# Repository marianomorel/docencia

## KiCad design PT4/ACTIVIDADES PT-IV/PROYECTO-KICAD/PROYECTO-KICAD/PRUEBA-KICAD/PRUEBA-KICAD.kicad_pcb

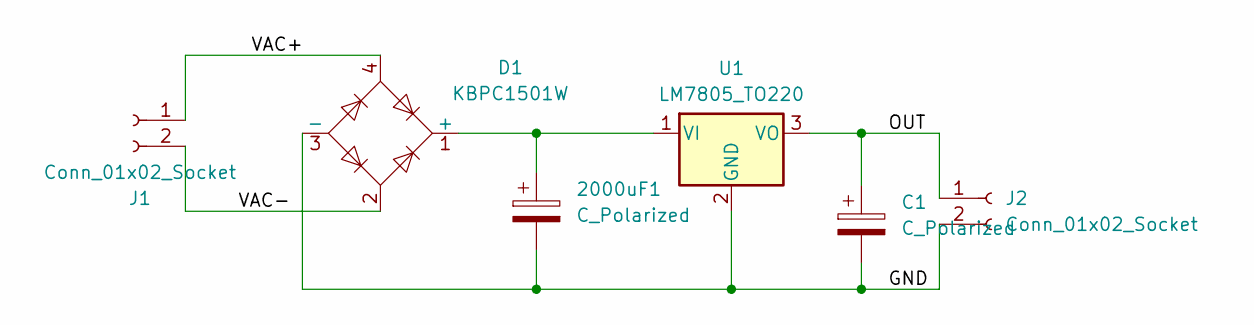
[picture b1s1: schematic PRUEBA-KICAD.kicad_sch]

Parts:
2000uF1: C_Polarized; C_Radial_D18.0mm_H35.5mm_P7.50mm
C1: C_Polarized; C_Radial_D5.0mm_H11.0mm_P2.00mm
D1: KBPC1501W; Diode_Bridge_GeneSiC_KBPC_W
J1, J2: Conn_01x02_Socket; TerminalBlock_MaiXu_MX126-5.0-02P_1x02_P5.00mm
U1: LM7805_TO220; TO-220-3_Vertical

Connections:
/GND: 2000uF1.2, C1.2, D1.3 (-), J2.2, U1.2 (GND)
/OUT: C1.1, J2.1, U1.3 (VO)
/VAC+: D1.4, J1.1
/VAC-: D1.2, J1.2
unnamed: 2000uF1.1, D1.1 (+), U1.1 (VI)

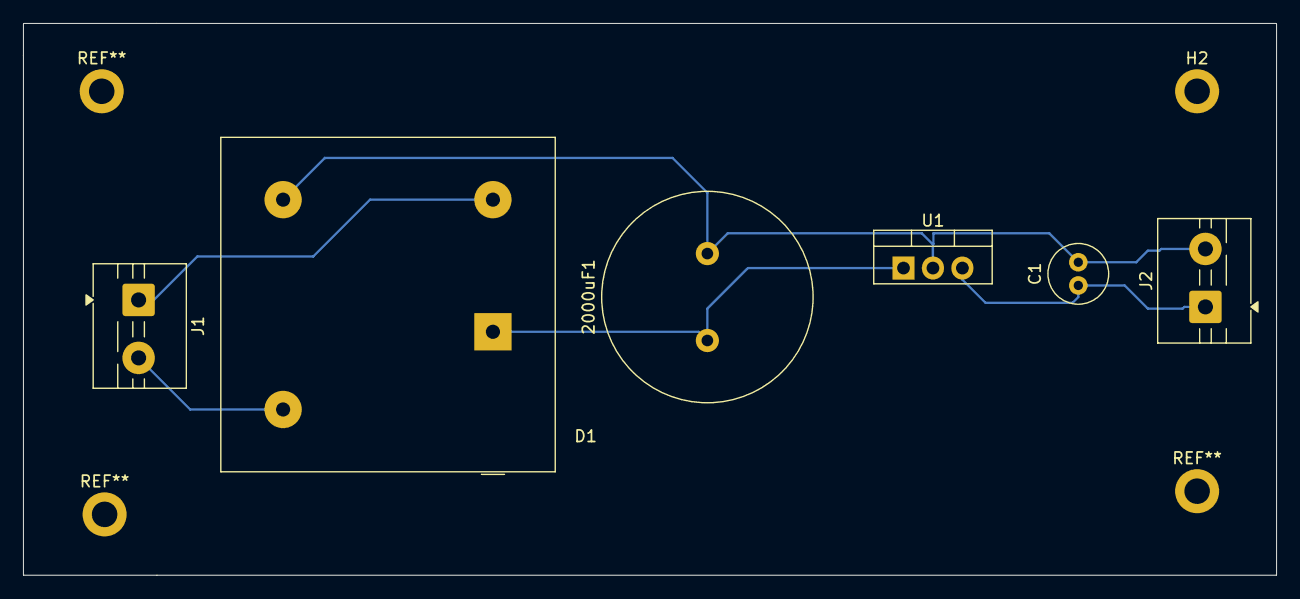
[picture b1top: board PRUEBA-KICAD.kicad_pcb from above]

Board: 2 copper layers, 108.1 x 47.6 mm, 7 parts (0 on the bottom side), 5 nets.

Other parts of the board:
H2: MountingHole_2.2mm_M2_DIN965_Pad

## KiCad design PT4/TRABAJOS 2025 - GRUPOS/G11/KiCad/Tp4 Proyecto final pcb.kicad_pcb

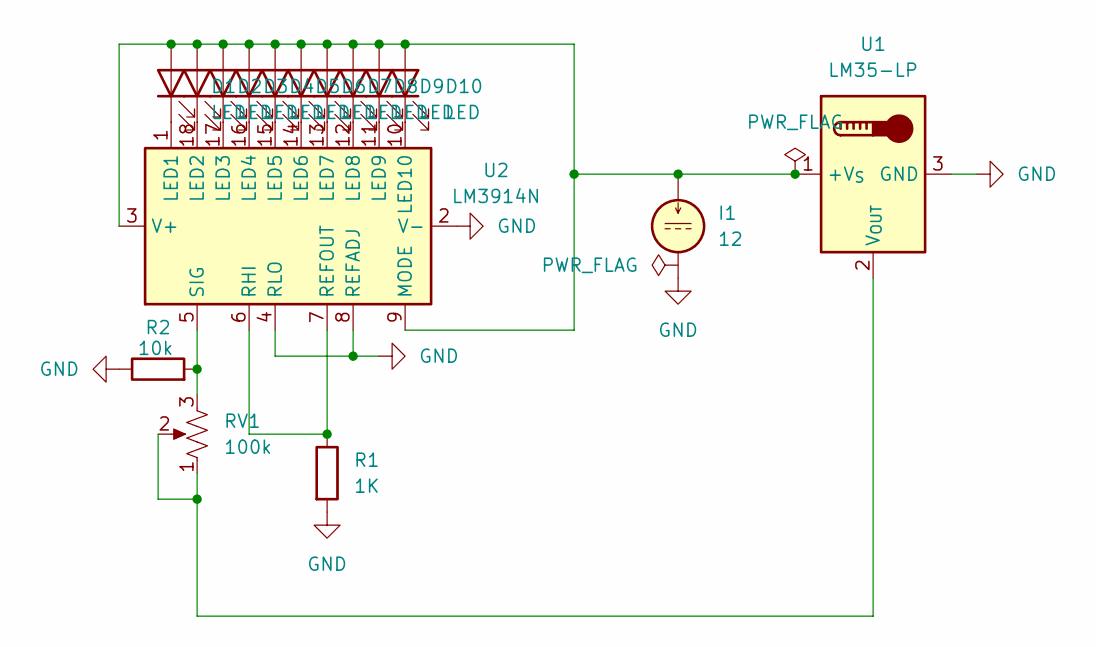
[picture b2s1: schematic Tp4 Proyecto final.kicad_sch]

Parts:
D1, D2, D3, D4, D5, D6, D7, D8, D9, D10: LED; LED_D5.0mm
I1: 12; SolderWire-0.1sqmm_1x02_P3.6mm_D0.4mm_OD1mm
R1: 1K; R_LDR_5.2x5.2mm_P3.5mm_Horizontal
R2: 10k; R_LDR_5.2x5.2mm_P3.5mm_Horizontal
RV1: 100k; Potentiometer_Piher_PT-10-V05_Vertical
U1: LM35-LP; TO-92_Inline_Wide
U2: LM3914N; DIP-18_W7.62mm

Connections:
GND: I1.2, R1.2, R2.1, U1.3 (GND), U2.2 (V-), U2.4 (RLO), U2.8 (REFADJ)
unnamed: D1.2 (A), D2.2 (A), D3.2 (A), D4.2 (A), D5.2 (A), D6.2 (A), D7.2 (A), D8.2 (A), D9.2 (A), D10.2 (A), I1.1, U1.1 (+V_{S}), U2.3 (V+), U2.9 (MODE)
unnamed: D1.1 (K), U2.1 (LED1)
unnamed: D2.1 (K), U2.18 (LED2)
unnamed: D3.1 (K), U2.17 (LED3)
unnamed: D4.1 (K), U2.16 (LED4)
unnamed: D5.1 (K), U2.15 (LED5)
unnamed: D6.1 (K), U2.14 (LED6)
unnamed: D7.1 (K), U2.13 (LED7)
unnamed: D8.1 (K), U2.12 (LED8)
unnamed: D9.1 (K), U2.11 (LED9)
unnamed: D10.1 (K), U2.10 (LED10)
unnamed: RV1.1, RV1.2, U1.2 (V_{OUT})
unnamed: R1.1, U2.6 (RHI), U2.7 (REFOUT)
unnamed: R2.2, RV1.3, U2.5 (SIG)

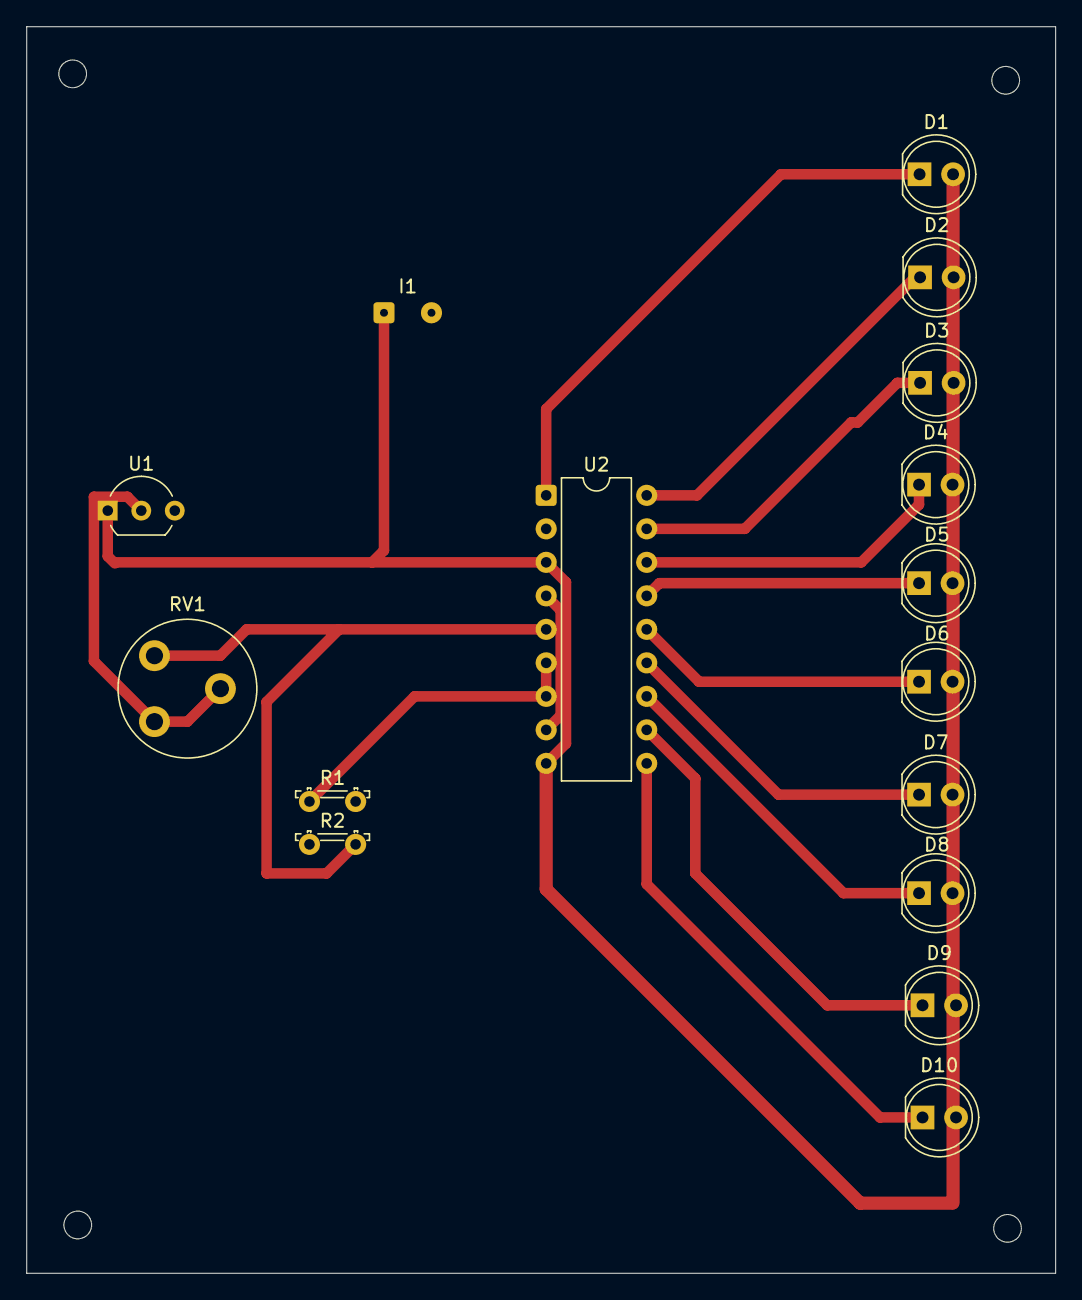
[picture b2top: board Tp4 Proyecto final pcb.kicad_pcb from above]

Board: 2 copper layers, 78.0 x 94.5 mm, 16 parts (0 on the bottom side), 15 nets.

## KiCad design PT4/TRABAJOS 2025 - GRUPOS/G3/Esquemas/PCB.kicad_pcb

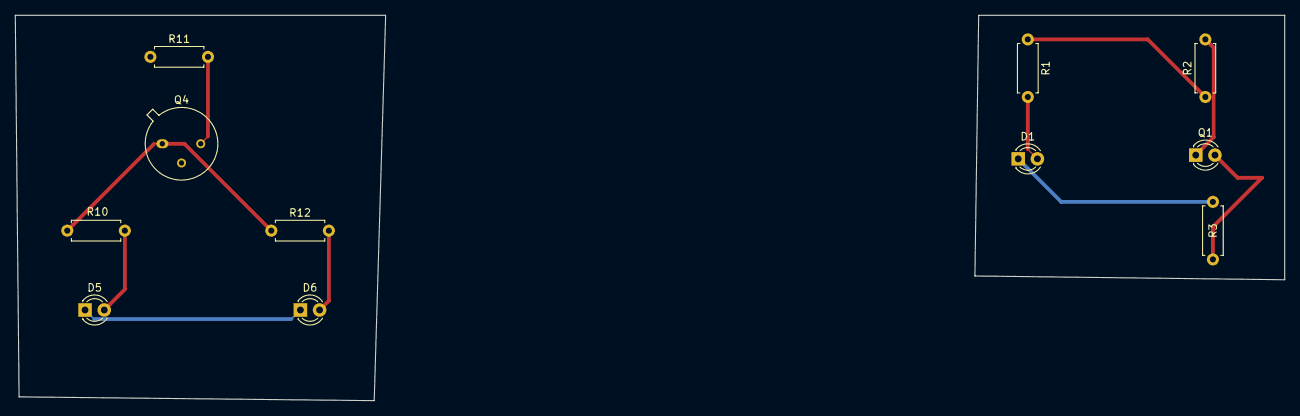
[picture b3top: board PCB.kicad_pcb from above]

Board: 2 copper layers, 168.0 x 51.0 mm, 11 parts (0 on the bottom side), 9 nets.

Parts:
D1, D5, D6: IR204A; LED_D3.0mm_IRBlack
Q1: TEPT4400; LED_D3.0mm_Clear
Q4: 2N2219; TO-39-3
R1, R2, R10, R12: 220; R_Axial_DIN0207_L6.3mm_D2.5mm_P7.62mm_Horizontal
R3, R11: 10k; R_Axial_DIN0207_L6.3mm_D2.5mm_P7.62mm_Horizontal

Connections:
+5V: R1.1, R2.1, R11.1
GND: D1.1 (K), D5.1 (K), D6.1 (K), R3.2
unnamed: Q1.2 (E), R3.1
unnamed: D1.2 (A), R1.2
unnamed: D5.2 (A), R10.2
unnamed: D6.2 (A), R12.2
unnamed: Q1.1 (C), R2.2
unnamed: Q4.3 (C), R11.2
unnamed: Q4.1 (E), R10.1, R12.1

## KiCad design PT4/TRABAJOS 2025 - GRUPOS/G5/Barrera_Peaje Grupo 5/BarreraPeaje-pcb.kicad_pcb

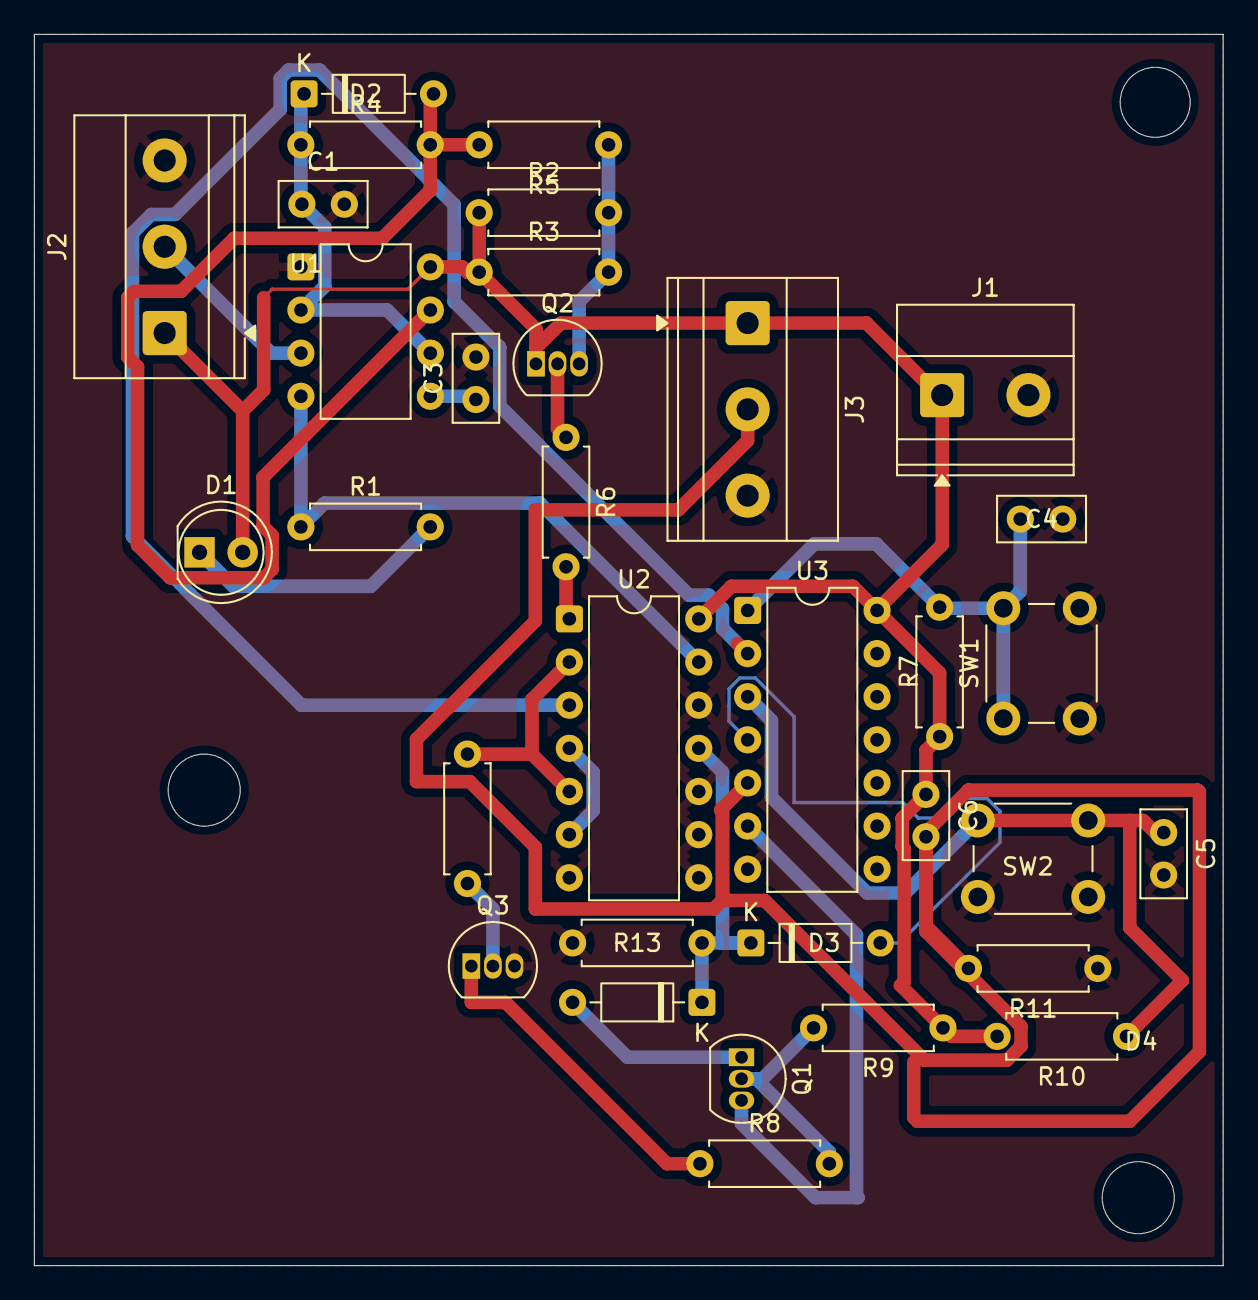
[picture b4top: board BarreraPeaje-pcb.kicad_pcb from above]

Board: 2 copper layers, 70.0 x 72.5 mm, 33 parts (0 on the bottom side), 24 nets.

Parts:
C1: 10nF; C_Disc_D5.0mm_W2.5mm_P2.50mm
C3, C4, C5, C6: 100nF; C_Disc_D5.0mm_W2.5mm_P2.50mm
D1: LED; LED_D5.0mm
D2, D3, D4: 1N4148; D_DO-35_SOD27_P7.62mm_Horizontal
J1: Alimentacion 12V; TerminalBlock_Phoenix_MKDS-1,5-2-5.08_1x02_P5.08mm_Horizont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
J2: Salida/Servo; TerminalBlock_Phoenix_MKDS-1,5-3-5.08_1x03_P5.08mm_Horizont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
J3: Sensor en Barrera; TerminalBlock_Phoenix_MKDS-1,5-3-5.08_1x03_P5.08mm_Horizont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
Q1: BC558; TO-92_Inline
Q2, Q3: BC548; TO-92_Inline
R1, R6, R7, R10, R11, R13: 10k; R_Axial_DIN0207_L6.3mm_D2.5mm_P7.62mm_Horizontal
R2: 47k; R_Axial_DIN0207_L6.3mm_D2.5mm_P7.62mm_Horizontal
R3, R9: 15k; R_Axial_DIN0207_L6.3mm_D2.5mm_P7.62mm_Horizontal
R4: 270k; R_Axial_DIN0207_L6.3mm_D2.5mm_P7.62mm_Horizontal
R5: 180; R_Axial_DIN0207_L6.3mm_D2.5mm_P7.62mm_Horizontal
R8, R12: 1k; R_Axial_DIN0207_L6.3mm_D2.5mm_P7.62mm_Horizontal
SW1: Open/Close; SW_PUSH_6mm_H4.3mm
SW2: Marcha/Stop; SW_PUSH_6mm_H4.3mm
U1: LM555xN; DIP-8_W7.62mm
U2: 4013; DIP-14_W7.62mm
U3: 40106; DIP-14_W7.62mm

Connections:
+5V: C6.1, D1.2 (A), J1.1, J2.1, J3.1, Q2.1 (C), R2.1, R3.1, R7.1, R9.1, R10.2, U1.8 (VCC), U2.14 (VDD), U3.14 (VDD)
GND: C1.2, C3.2, C4.2, C5.2, J1.2, J2.3, J3.3, Q3.3 (E), R11.1, R13.2, SW1.2, SW2.1, U1.1 (GND), U2.7 (VSS), U2.8 (S), U2.9 (D), U2.10 (R), U2.12 (~Q), U3.7 (VSS)
unnamed: C4.1, R7.2, SW1.1, U3.1
unnamed: C5.1, R10.1, SW2.2, U3.3
unnamed: D1.1 (K), R1.2
unnamed: D2.2 (A), R4.2, R5.2, U1.7 (DIS)
unnamed: C1.1, D2.1 (K), R4.1, U1.2 (TR), U1.6 (THR)
unnamed: D3.2 (A), U3.4
unnamed: D3.1 (K), D4.1 (K), R13.1, U2.11 (C)
unnamed: D4.2 (A), Q1.1 (C)
unnamed: J2.2, U1.3 (Q)
unnamed: C6.2, J3.2, R11.2, U3.5
unnamed: Q1.2 (B), R8.2, R9.2
unnamed: Q1.3 (E), U3.6
unnamed: Q2.2 (B), R6.1
unnamed: Q2.3 (E), R2.2, R3.2, R5.1
unnamed: Q3.2 (B), R12.2
unnamed: Q3.1 (C), R8.1
unnamed: C3.1, U1.5 (CV)
unnamed: R1.1, U1.4 (R), U2.13 (Q)
unnamed: U2.3 (C), U3.2
unnamed: R12.1, U2.2 (~Q), U2.5 (D)
unnamed: R6.2, U2.1 (Q)
unnamed: U2.4 (R), U2.6 (S)

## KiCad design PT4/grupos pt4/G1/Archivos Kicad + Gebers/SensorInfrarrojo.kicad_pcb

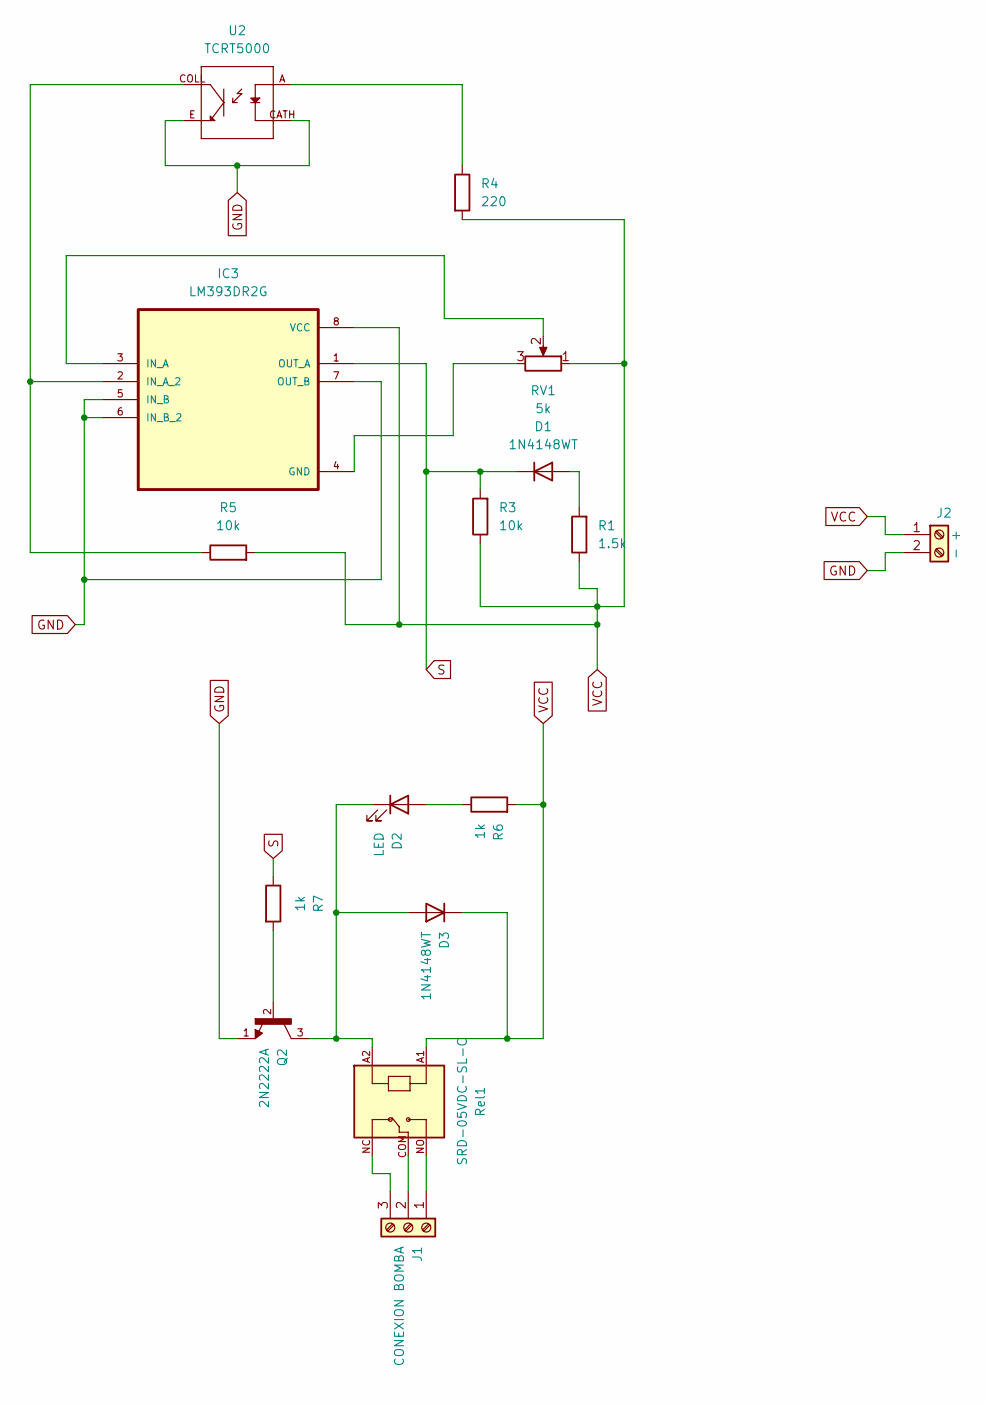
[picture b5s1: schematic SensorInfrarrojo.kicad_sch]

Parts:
D1, D3: 1N4148WT; D_SOD-523
D2: LED; LED_0402_1005Metric_Pad0.77x0.64mm_HandSolder
IC3: LM393DR2G; SOIC127P600X265-8N
J1: CONEXION BOMBA; TerminalBlock_Phoenix_MKDS-1,5-3_1x03_P5.00mm_Horizontal
J2: - +; TerminalBlock_MaiXu_MX126-5.0-02P_1x02_P5.00mm
Q2: 2N2222A; TO92254P470H750-3; PARTREV N/A
R1: 1.5k; R_0603_1608Metric_Pad0.98x0.95mm_HandSolder
R3, R5: 10k; R_0603_1608Metric_Pad0.98x0.95mm_HandSolder
R4: 220; R_0603_1608Metric_Pad0.98x0.95mm_HandSolder
R6, R7: 1k; R_Axial_DIN0204_L3.6mm_D1.6mm_P5.08mm_Horizontal
RV1: 5k; Potentiometer_Bourns_3296W_Vertical
Rel1: SRD-05VDC-SL-C; RELAY_SRD-05VDC-SL-C
U2: TCRT5000; OPTO_TCRT5000; PARTREV 1.7

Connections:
GND: IC3.5 (IN_B), IC3.6 (IN_B_2), IC3.7 (OUT_B), J2.2, Q2.1, U2.CATH, U2.E
unnamed: D1.2 (A), R1.2
unnamed: D2.2 (A), R6.1
unnamed: D2.1 (K), D3.2 (A), Q2.3, Rel1.A2
unnamed: IC3.4 (GND), RV1.3
unnamed: IC3.3 (IN_A), RV1.2
unnamed: IC3.2 (IN_A_2), R5.1, U2.COLL
unnamed: J1.1, Rel1.NO
unnamed: J1.2, Rel1.COM
unnamed: J1.3, Rel1.NC
unnamed: Q2.2, R7.2
unnamed: R4.1, U2.A
S: D1.1 (K), IC3.1 (OUT_A), R3.2, R7.1
VCC: D3.1 (K), IC3.8 (VCC), J2.1, R1.1, R3.1, R4.2, R5.2, R6.2, RV1.1, Rel1.A1

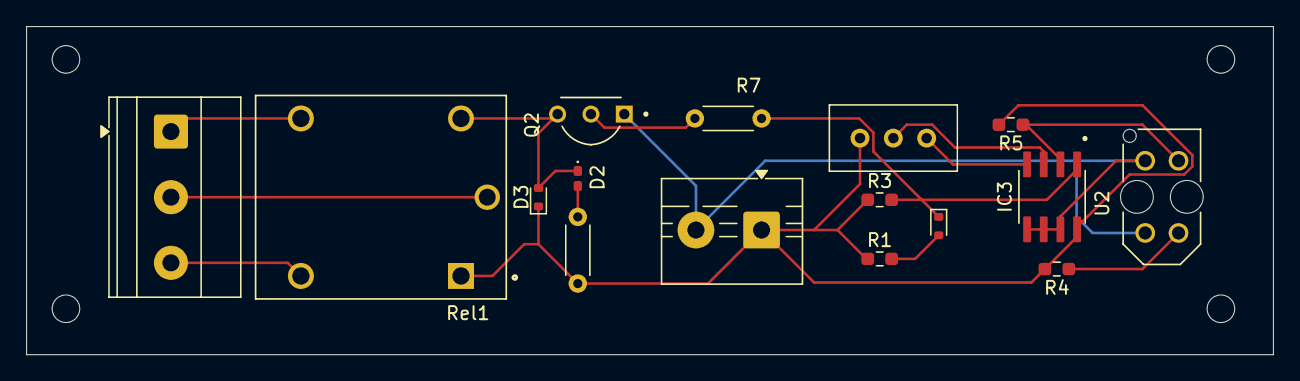
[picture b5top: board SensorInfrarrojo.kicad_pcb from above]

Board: 2 copper layers, 95.0 x 25.0 mm, 16 parts (0 on the bottom side), 14 nets.

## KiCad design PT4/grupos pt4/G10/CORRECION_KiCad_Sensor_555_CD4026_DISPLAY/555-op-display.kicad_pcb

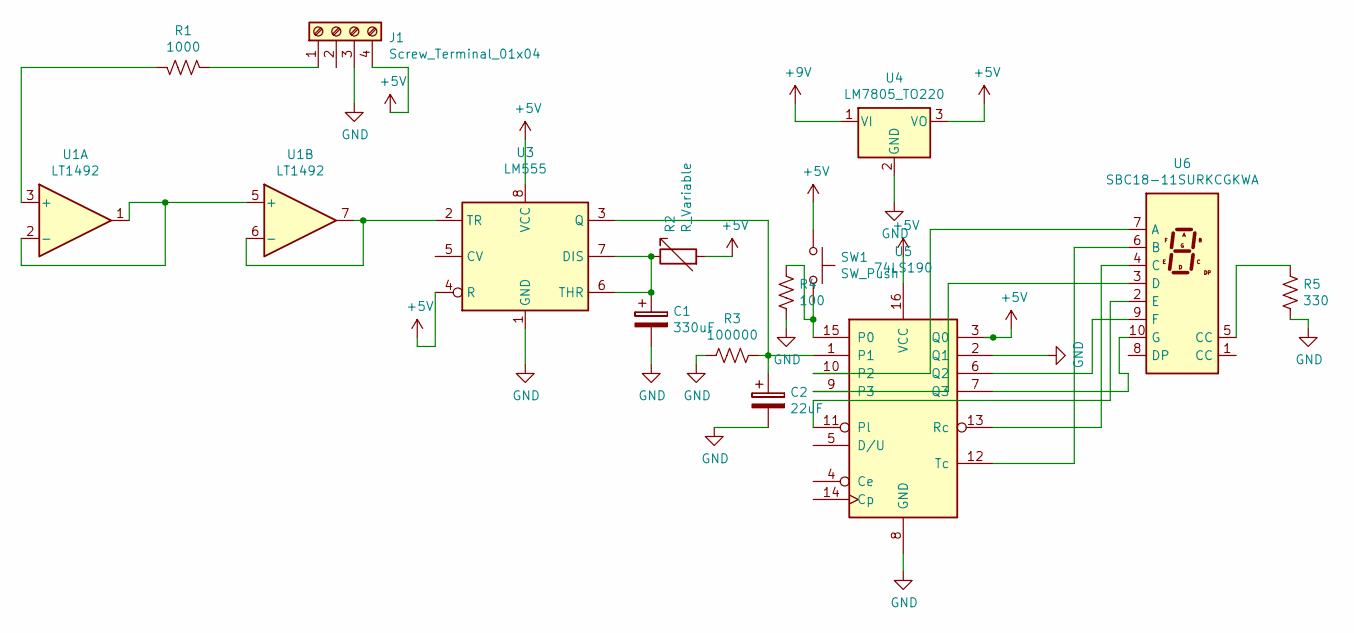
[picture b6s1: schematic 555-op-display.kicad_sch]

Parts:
C1: 330uF; CP_Radial_D5.0mm_P2.50mm
C2: 22uF; CP_Radial_D5.0mm_P2.50mm
J1: Screw_Terminal_01x04; TerminalBlock_bornier-4_P5.08mm
R1: 1000; R_Axial_DIN0204_L3.6mm_D1.6mm_P5.08mm_Horizontal
R2: R_Variable; Potentiometer_Trimmer_ACP_CA6v_Horizontal
R3: 100000; R_Axial_DIN0207_L6.3mm_D2.5mm_P7.62mm_Horizontal
R4: 100; R_Axial_DIN0207_L6.3mm_D2.5mm_P7.62mm_Horizontal
R5: 330; R_Axial_DIN0207_L6.3mm_D2.5mm_P7.62mm_Horizontal
SW1: SW_Push; KSA_Tactile_SPST
U1: LT1492; DIP-8_W7.62mm
U3: LM555; DIP-8_W7.62mm
U4: LM7805_TO220; TO-220-3_Vertical
U5: 74LS190; DIP-16_W7.62mm
U6: SBC18-11SURKCGKWA; 7SEGMENT-LED__HDSM531_HDSM533_SMD

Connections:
+5V: J1.4, R2.2, SW1.1, U3.4 (R), U3.8 (VCC), U4.3 (VO), U5.3 (Q0), U5.16 (VCC)
+9V: U4.1 (VI)
GND: C1.2, C2.2, J1.3, R3.2, R4.2, R5.2, U3.1 (GND), U4.2 (GND), U5.2 (Q1), U5.8 (GND)
unnamed: J1.1, R1.1
unnamed: R5.1, U6.5 (CC)
unnamed: R1.2, U1.3 (+)
unnamed: U1.1, U1.2 (-), U1.5 (+)
unnamed: U1.6 (-), U1.7, U3.2 (TR)
unnamed: C1.1, R2.1, U3.6 (THR), U3.7 (DIS)
unnamed: C2.1, R3.1, U3.3 (Q), U5.1
unnamed: R4.1, SW1.2, U5.15 (P0)
unnamed: U5.10 (P2), U6.7 (A)
unnamed: U5.9 (P3), U6.3 (D)
unnamed: U5.11 (Pl), U6.2 (E)
unnamed: U5.6 (Q2), U6.9 (F)
unnamed: U5.7 (Q3), U6.10 (G)
unnamed: U5.13 (Rc), U6.4 (C)
unnamed: U5.12 (Tc), U6.6 (B)

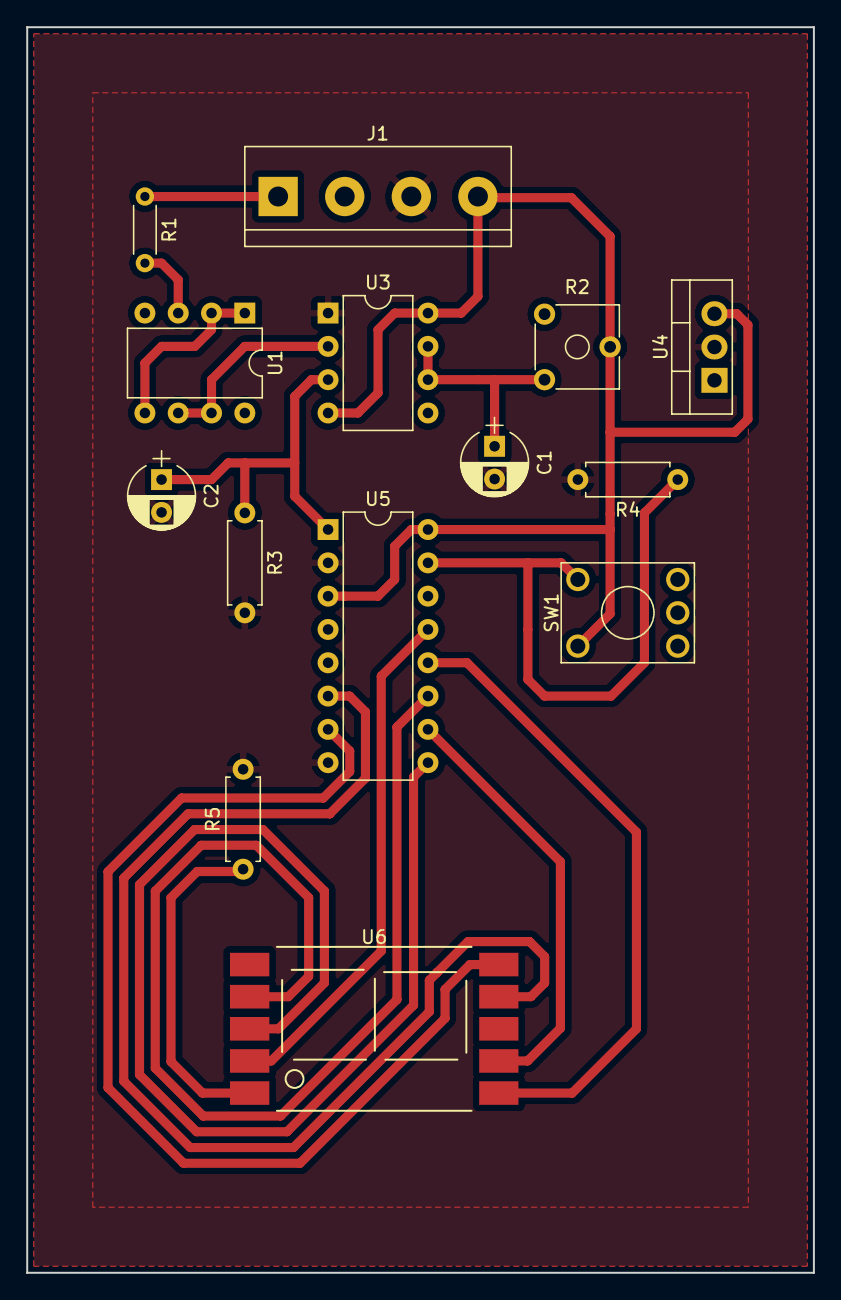
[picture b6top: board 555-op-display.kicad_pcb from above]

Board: 2 copper layers, 60.0 x 95.0 mm, 14 parts (0 on the bottom side), 17 nets.
